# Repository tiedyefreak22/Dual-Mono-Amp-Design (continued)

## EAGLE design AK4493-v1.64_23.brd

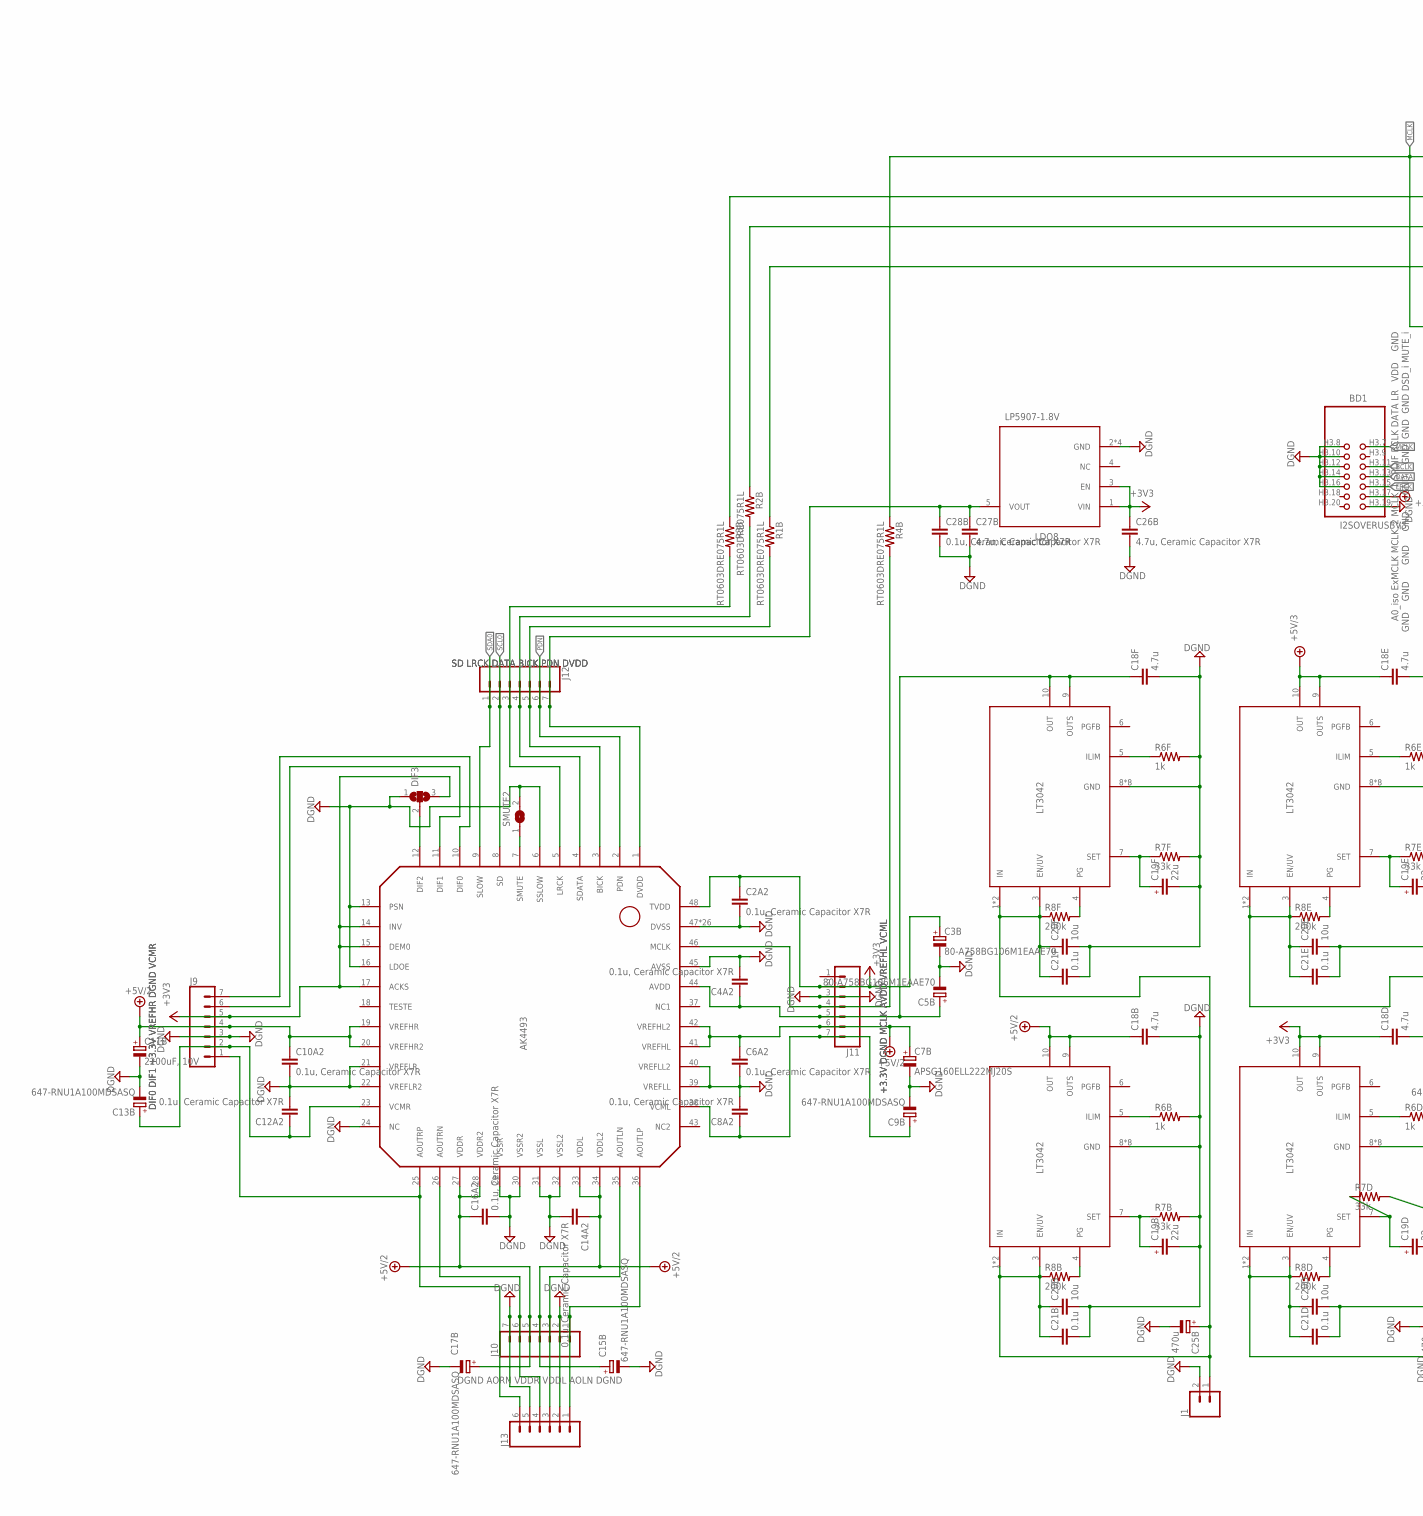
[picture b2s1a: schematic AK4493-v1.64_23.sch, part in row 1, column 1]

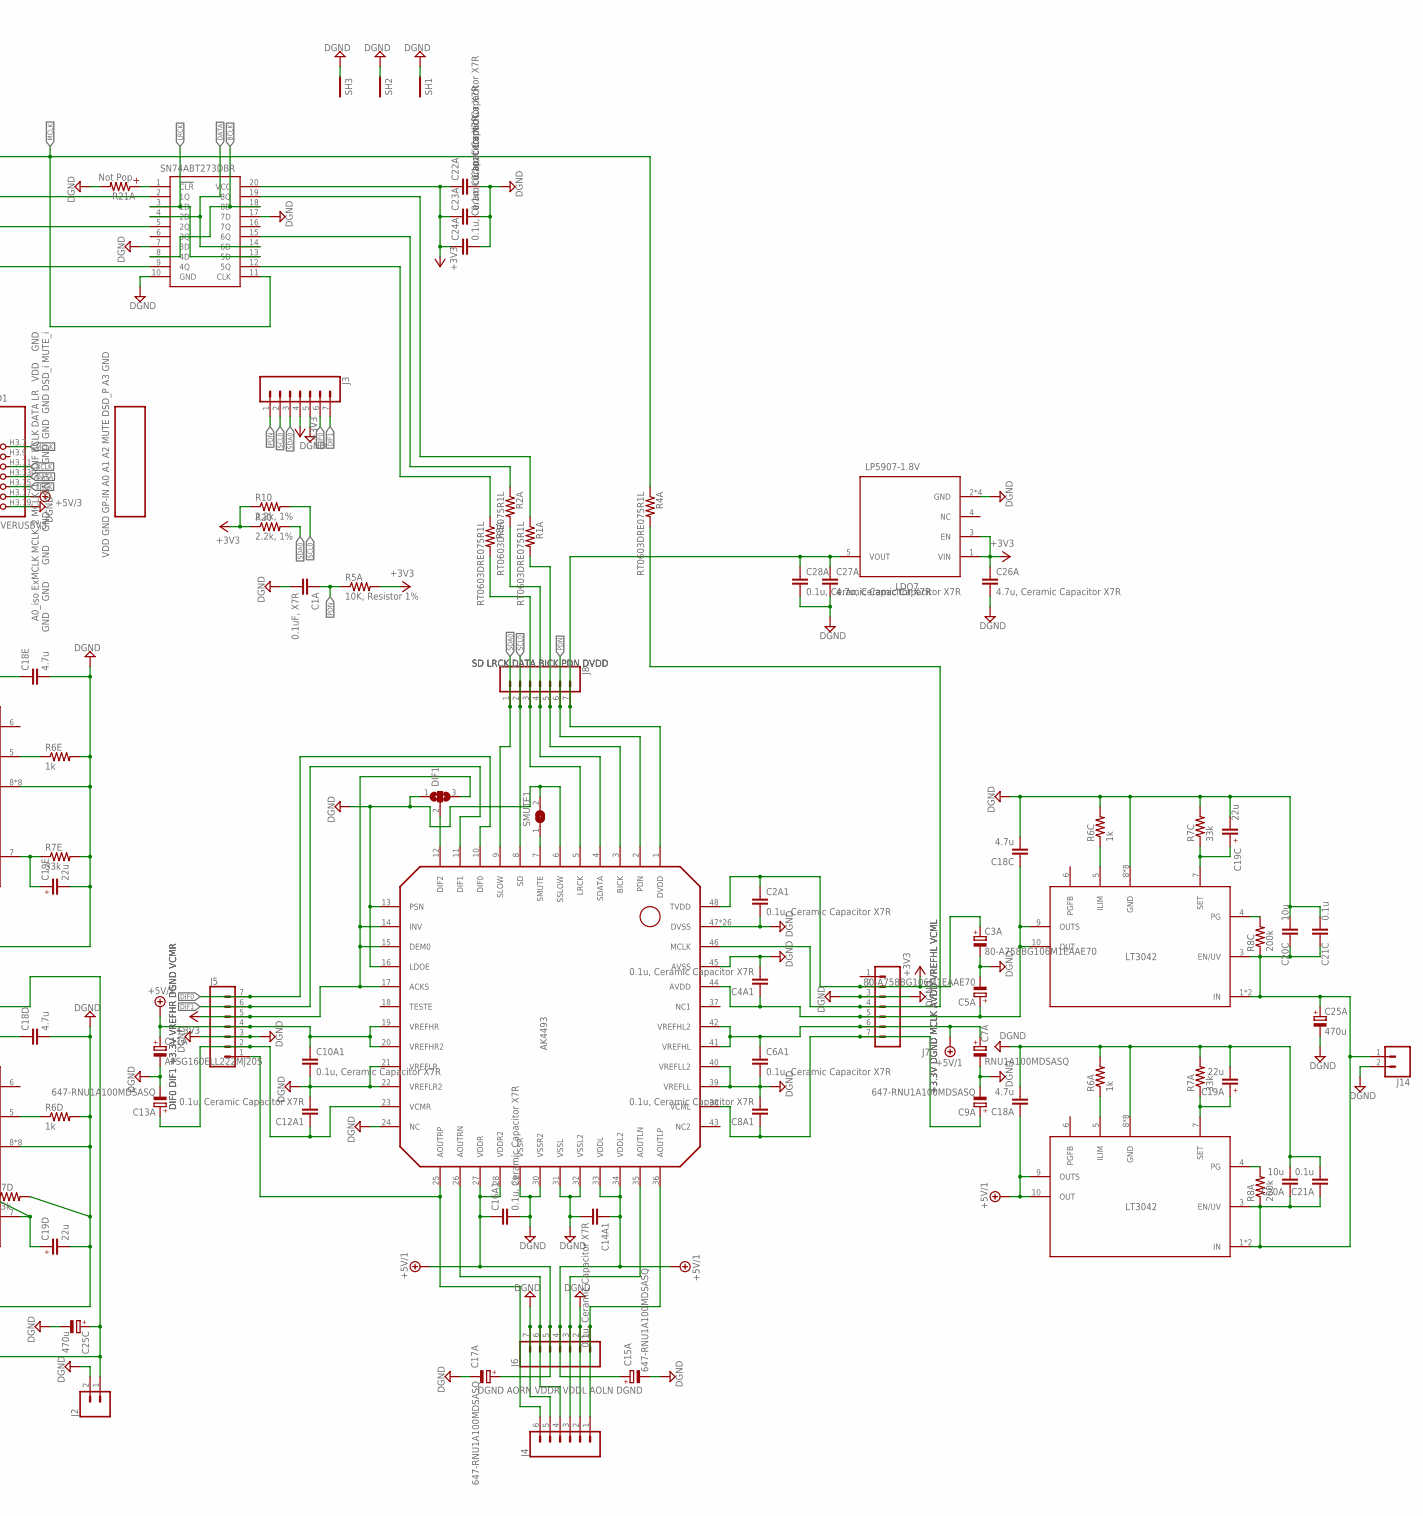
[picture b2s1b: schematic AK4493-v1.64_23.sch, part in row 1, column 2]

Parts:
BD1: I2SOVERUSBV3
C1A: 0.1uF, X7R; CAPC2012X135N
C2A1, C2A2, C4A1, C4A2, C6A1, C6A2, C8A1, C8A2, C10A1, C10A2, C12A1, C12A2, C14A1, C14A2, C16A1, C16A2: 0.1u, Ceramic Capacitor X7R; CAPC1608X95N
C3A: 80-A758BG106M1EAAE70; CAPPRD150W45D450H600
C3B, C5A, C5B: 80-A758BG106M1EAAE70; CAPPRD200W55D500H800
C7A: RNU1A100MDSASQ; CAPPRD150W45D450H600
C7B, C11A: APSG160ELL222MJ20S; CAPPRD500W60D1025H2150
C9A, C9B, C13A, C13B, C15A, C15B, C17A, C17B: 647-RNU1A100MDSASQ; CAPPRD150W45D450H600
C11B: 2200uF, 10V; CAPPRD500W60D1025H2150
C18A, C18B, C18C, C18D, C18E, C18F: 4.7u; CAPC2013X140N
C19A, C19B, C19C, C19D, C19E, C19F: 22u; C1206
C20A, C20B, C20C, C20D, C20E, C20F: 10u; CAPC2012X135N
C21A, C21B, C21C, C21D, C21E, C21F: 0.1u; CAPC2012X135N
C22A, C23A, C24A, C28A, C28B: 0.1u, Ceramic Capacitor X7R; CAPC2012X135N
C25A, C25B, C25C: 470u; CAPPRD350W60D825H1300
C26A, C26B, C27A, C27B: 4.7u, Ceramic Capacitor X7R; CAPC2013X140N
DIF1, DIF3: SJ2W; SJ_2
IC2, IC3: AK4493; LQFP48_
IC4A: SN74ABT273DBR; SOP65P780X200-20N
J1, J2, J14: CONN_02; 1X02
J3, J5, J6, J7, J8, J9, J10, J11, J12: CONN_07; 1X07
J4, J13: CONN_06SILK_FEMALE_PTH; 1X06
LDO1, LDO2, LDO3, LDO4, LDO5, LDO6: LT3042; SOP50P490X110-11N
LDO7, LDO8: LP5907-1.8V; SOT95P280X145-5N
R1A, R1B, R2A, R2B, R3A, R3B, R4A, R4B: RT0603DRE075R1L; RESC1608X55N
R5A: 10K, Resistor 1%; RESC2012X50N
R6A, R6B, R6C, R6D, R6E, R6F: 1k; RESC2012X60N
R7A, R7B, R7C, R7D, R7E, R7F: 33k; R0805
R8A, R8B, R8C, R8D, R8E, R8F: 200k; R0805
R10, R20: 2.2k, 1%; RCS0805_E3
R21A: Not Pop.; R0805-POL
SH1, SH2, SH3: SHORTA5; SHORT_ALL-50
SMUTE1, SMUTE2: SJ

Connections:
+3V3: C2A1.1, C2A2.1, C3A.1 (+), C3B.1 (+), C18D.1, C22A.1, C23A.1, C24A.1, C26A.1, C26B.1, DIF1.3, DIF3.3, IC2.14 (INV), IC2.15 (DEM0), IC2.17 (ACKS), IC2.48 (TVDD), IC3.14 (INV), IC3.15 (DEM0), IC3.17 (ACKS), IC3.48 (TVDD), IC4A.20 (VCC), J3.4, J5.5, J7.2, J9.5, J11.2, LDO4.9 (OUTS), LDO4.10 (OUT), LDO7.1 (VIN), LDO7.3 (EN), LDO8.1 (VIN), LDO8.3 (EN), R5A.2, R10.1, R20.1
+5V/1: C6A1.1, C7A.1 (+), C10A1.1, C11A.1 (+), C14A1.1, C15A.1 (+), C16A1.1, C17A.1 (+), C18A.1, IC2.19 (VREFHR), IC2.20 (VREFHR2), IC2.27 (VDDR), IC2.28 (VDDR2), IC2.33 (VDDL), IC2.34 (VDDL2), IC2.41 (VREFHL), IC2.42 (VREFHL2), J5.4, J6.4, J6.5, J7.6, LDO1.9 (OUTS), LDO1.10 (OUT)
+5V/2: C6A2.1, C7B.1 (+), C10A2.1, C11B.1 (+), C14A2.1, C15B.1 (+), C16A2.1, C17B.1 (+), C18B.1, IC3.19 (VREFHR), IC3.20 (VREFHR2), IC3.27 (VDDR), IC3.28 (VDDR2), IC3.33 (VDDL), IC3.34 (VDDL2), IC3.41 (VREFHL), IC3.42 (VREFHL2), J9.4, J10.4, J10.5, J11.6, LDO2.9 (OUTS), LDO2.10 (OUT)
+5V/3: BD1.H3.17, C18E.1, LDO5.9 (OUTS), LDO5.10 (OUT)
BCLK: BD1.H3.11, IC4A.8 (4D), IC4A.18 (8D)
DATA: BD1.H3.13, IC4A.4 (2D), IC4A.14 (6D)
DGND: BD1.H3.8, BD1.H3.10, BD1.H3.12, BD1.H3.14, BD1.H3.16, BD1.H3.19, C1A.2, C2A1.2, C2A2.2, C3A.2 (-), C3B.2 (-), C4A1.2, C4A2.2, C5A.2 (-), C5B.2 (-), C6A1.2, C6A2.2, C7A.2 (-), C7B.2 (-), C8A1.2, C8A2.2, C9A.2 (-), C9B.2 (-), C10A1.2, C10A2.2, C11A.2 (-), C11B.2 (-), C12A1.2, C12A2.2, C13A.2 (-), C13B.2 (-), C14A1.2, C14A2.2, C15A.2 (-), C15B.2 (-), C16A1.2, C16A2.2, C17A.2 (-), C17B.2 (-), C18A.2, C18B.2, C18C.2, C18D.2, C18E.2, C18F.2, C19A.2, C19A.DGND (2), C19B.2, C19B.DGND (2), C19C.2, C19C.DGND (2), C19D.2, C19D.DGND (2), C19E.2, C19E.DGND (2), C19F.2, C19F.DGND (2), C20A.2, C20B.2, C20C.2, C20D.2, C20E.2, C20F.2, C21A.2, C21B.2, C21C.2, C21D.2, C21E.2, C21F.2, C22A.2, C23A.2, C24A.2, C25A.2 (-), C25B.2 (-), C25C.2 (-), C26A.2, C26B.2, C27A.2, C27B.2, C28A.2, C28B.2, DIF1.1, DIF3.1, IC2.6 (SSLOW), IC2.13 (PSN), IC2.16 (LDOE), IC2.21 (VREFLR), IC2.22 (VREFLR2), IC2.24 (NC), IC2.29 (VSSR), IC2.30 (VSSR2), IC2.31 (VSSL), IC2.32 (VSSL2), IC2.39 (VREFLL), IC2.40 (VREFLL2), IC2.45 (AVSS), IC2.47 (DVSS), IC2.P$1 (DVSS), IC2.P$2 (DVSS), IC2.P$3 (DVSS), IC2.P$4 (DVSS), IC2.P$5 (DVSS), IC2.P$6 (DVSS), IC2.P$7 (DVSS), IC2.P$8 (DVSS), IC2.P$9 (DVSS), IC2.P$10 (DVSS), IC2.P$11 (DVSS), IC2.P$12 (DVSS), IC2.P$13 (DVSS), IC2.P$14 (DVSS), IC2.P$15 (DVSS), IC2.P$16 (DVSS), IC2.P$17 (DVSS), IC2.P$18 (DVSS), IC2.P$19 (DVSS), IC2.P$20 (DVSS), IC2.P$21 (DVSS), IC2.P$22 (DVSS), IC2.P$23 (DVSS), IC2.P$24 (DVSS), IC2.P$25 (DVSS), IC3.6 (SSLOW), IC3.13 (PSN), IC3.16 (LDOE), IC3.21 (VREFLR), IC3.22 (VREFLR2), IC3.24 (NC), IC3.29 (VSSR), IC3.30 (VSSR2), IC3.31 (VSSL), IC3.32 (VSSL2), IC3.39 (VREFLL), IC3.40 (VREFLL2), IC3.45 (AVSS), IC3.47 (DVSS), IC3.P$1 (DVSS), IC3.P$2 (DVSS), IC3.P$3 (DVSS), IC3.P$4 (DVSS), IC3.P$5 (DVSS), IC3.P$6 (DVSS), IC3.P$7 (DVSS), IC3.P$8 (DVSS), IC3.P$9 (DVSS), IC3.P$10 (DVSS), IC3.P$11 (DVSS), IC3.P$12 (DVSS), IC3.P$13 (DVSS), IC3.P$14 (DVSS), IC3.P$15 (DVSS), IC3.P$16 (DVSS), IC3.P$17 (DVSS), IC3.P$18 (DVSS), IC3.P$19 (DVSS), IC3.P$20 (DVSS), IC3.P$21 (DVSS), IC3.P$22 (DVSS), IC3.P$23 (DVSS), IC3.P$24 (DVSS), IC3.P$25 (DVSS), IC4A.7 (3D), IC4A.10 (GND), IC4A.17 (7D), J1.2, J2.2, J3.5, J4.2, J4.5, J5.3, J6.2, J6.7, J7.3, J9.3, J10.2, J10.7, J11.3, J13.2, J13.5, J14.2, LDO1.8 (GND), LDO1.11 (GND), LDO1.P$1 (GND), LDO1.P$2 (GND), LDO1.P$3 (GND), LDO1.P$4 (GND), LDO1.P$5 (GND), LDO1.P$6 (GND), LDO2.8 (GND), LDO2.11 (GND), LDO2.P$1 (GND), LDO2.P$2 (GND), LDO2.P$3 (GND), LDO2.P$4 (GND), LDO2.P$5 (GND), LDO2.P$6 (GND), LDO3.8 (GND), LDO3.11 (GND), LDO3.P$1 (GND), LDO3.P$2 (GND), LDO3.P$3 (GND), LDO3.P$4 (GND), LDO3.P$5 (GND), LDO3.P$6 (GND), LDO4.8 (GND), LDO4.11 (GND), LDO4.P$1 (GND), LDO4.P$2 (GND), LDO4.P$3 (GND), LDO4.P$4 (GND), LDO4.P$5 (GND), LDO4.P$6 (GND), LDO5.8 (GND), LDO5.11 (GND), LDO5.P$1 (GND), LDO5.P$2 (GND), LDO5.P$3 (GND), LDO5.P$4 (GND), LDO5.P$5 (GND), LDO5.P$6 (GND), LDO6.8 (GND), LDO6.11 (GND), LDO6.P$1 (GND), LDO6.P$2 (GND), LDO6.P$3 (GND), LDO6.P$4 (GND), LDO6.P$5 (GND), LDO6.P$6 (GND), LDO7.2 (GND), LDO7.DGND (GND), LDO7.DGND2 (GND), LDO7.DGND3 (GND), LDO8.2 (GND), LDO8.DGND (GND), LDO8.DGND2 (GND), LDO8.DGND3 (GND), R6A.2, R6B.2, R6C.2, R6D.2, R6E.2, R6F.2, R7A.2, R7B.2, R7C.2, R7D.2, R7E.2, R7F.2, R21A.2, R21A.DGND (2), SH1.1, SH2.1, SH3.1, SMUTE1.2, SMUTE2.2
DIF0: IC2.10 (DIF0), J3.6, J5.7
DIF1: IC2.11 (DIF1), J3.7, J5.6
LRCK: BD1.H3.15, IC4A.3 (1D), IC4A.13 (5D)
MCLK: BD1.H3.7, IC4A.11 (CLK), R4A.1, R4B.1
unnamed: IC4A.1 (!CLR), R21A.1
unnamed: C8A2.1, C9B.1 (+), IC3.38 (VCML), J11.7
unnamed: C4A1.1, C5A.1 (+), C18C.1, IC2.44 (AVDD), J7.5, LDO3.9 (OUTS), LDO3.10 (OUT)
unnamed: LDO3.5 (ILIM), R6C.1
unnamed: LDO4.5 (ILIM), R6D.1
unnamed: C19D.1, LDO4.7 (SET), R7D.1
unnamed: LDO4.4 (PG), R8D.2
unnamed: LDO5.5 (ILIM), R6E.1
unnamed: C19E.1, LDO5.7 (SET), R7E.1
unnamed: IC3.46 (MCLK), J11.4, R4B.2
unnamed: LDO5.4 (PG), R8E.2
unnamed: C20D.1, C20E.1, C21D.1, C21E.1, C25C.1 (+), J2.1, LDO4.1 (IN), LDO4.2 (IN), LDO4.3 (EN/UV), LDO5.1 (IN), LDO5.2 (IN), LDO5.3 (EN/UV), R8D.1, R8E.1
unnamed: LDO1.5 (ILIM), R6A.1
unnamed: IC2.5 (LRCK), J8.3, R3A.2
unnamed: IC2.4 (SDATA), J8.4, R2A.2
unnamed: IC2.3 (BICK), J8.5, R1A.2
unnamed: C19A.1, LDO1.7 (SET), R7A.1
unnamed: IC4A.19 (8Q), R1A.1
unnamed: IC4A.15 (6Q), R2A.1
unnamed: IC4A.12 (5Q), R3A.1
unnamed: IC2.26 (AOUTRN), J4.4, J6.6
unnamed: IC3.3 (BICK), J12.5, R1B.2
unnamed: IC3.4 (SDATA), J12.4, R2B.2
unnamed: IC3.5 (LRCK), J12.3, R3B.2
unnamed: IC4A.9 (4Q), R1B.1
unnamed: IC4A.5 (2Q), R2B.1
unnamed: IC4A.2 (1Q), R3B.1
unnamed: LDO1.4 (PG), R8A.2
unnamed: LDO6.5 (ILIM), R6F.1
unnamed: C19F.1, LDO6.7 (SET), R7F.1
unnamed: C27A.1, C28A.1, IC2.1 (DVDD), J8.7, LDO7.5 (VOUT)
unnamed: LDO6.4 (PG), R8F.2
unnamed: C20A.1, C20C.1, C21A.1, C21C.1, C25A.1 (+), J14.1, LDO1.1 (IN), LDO1.2 (IN), LDO1.3 (EN/UV), LDO3.1 (IN), LDO3.2 (IN), LDO3.3 (EN/UV), R8A.1, R8C.1
unnamed: C4A2.1, C5B.1 (+), C18F.1, IC3.44 (AVDD), J11.5, LDO6.9 (OUTS), LDO6.10 (OUT)
unnamed: C19C.1, LDO3.7 (SET), R7C.1
unnamed: LDO3.4 (PG), R8C.2
unnamed: LDO2.5 (ILIM), R6B.1
unnamed: C19B.1, LDO2.7 (SET), R7B.1
unnamed: LDO2.4 (PG), R8B.2
unnamed: C20B.1, C20F.1, C21B.1, C21F.1, C25B.1 (+), J1.1, LDO2.1 (IN), LDO2.2 (IN), LDO2.3 (EN/UV), LDO6.1 (IN), LDO6.2 (IN), LDO6.3 (EN/UV), R8B.1, R8F.1
unnamed: C27B.1, C28B.1, IC3.1 (DVDD), J12.7, LDO8.5 (VOUT)
unnamed: C12A1.1, C13A.1 (+), IC2.23 (VCMR), J5.2
unnamed: IC3.36 (AOUTLP), J10.1, J13.1
unnamed: IC3.25 (AOUTRP), J9.1, J13.6
unnamed: IC3.10 (DIF0), J9.7
unnamed: IC2.36 (AOUTLP), J4.1, J6.1
unnamed: IC2.35 (AOUTLN), J4.3, J6.3
unnamed: IC3.35 (AOUTLN), J10.3, J13.3
unnamed: IC3.26 (AOUTRN), J10.6, J13.4
unnamed: IC2.25 (AOUTRP), J4.6, J5.1
unnamed: IC2.46 (MCLK), J7.4, R4A.2
unnamed: C12A2.1, C13B.1 (+), IC3.23 (VCMR), J9.2
unnamed: C8A1.1, C9A.1 (+), IC2.38 (VCML), J7.7
unnamed: DIF1.2, IC2.12 (DIF2)
unnamed: IC2.7 (SMUTE), SMUTE1.1
unnamed: DIF3.2, IC3.12 (DIF2)
unnamed: IC3.7 (SMUTE), SMUTE2.1
unnamed: IC3.11 (DIF1), J9.6
PDN: C1A.1, IC2.2 (PDN), IC3.2 (PDN), J3.1, J8.6, J12.6, R5A.1
SCL0: IC2.8 (SD), IC3.8 (SD), J3.2, J8.2, J12.2, R10.2
SDA0: IC2.9 (SLOW), IC3.9 (SLOW), J3.3, J8.1, J12.1, R20.2

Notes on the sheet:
+3.3V DGND MCLK AVDD VREFHL VCML
DIF0 DIF1 +3.3V VREFHR DGND VCMR
SD LRCK DATA BICK PDN DVDD
DGND AORN VDDR VDDL AOLN DGND

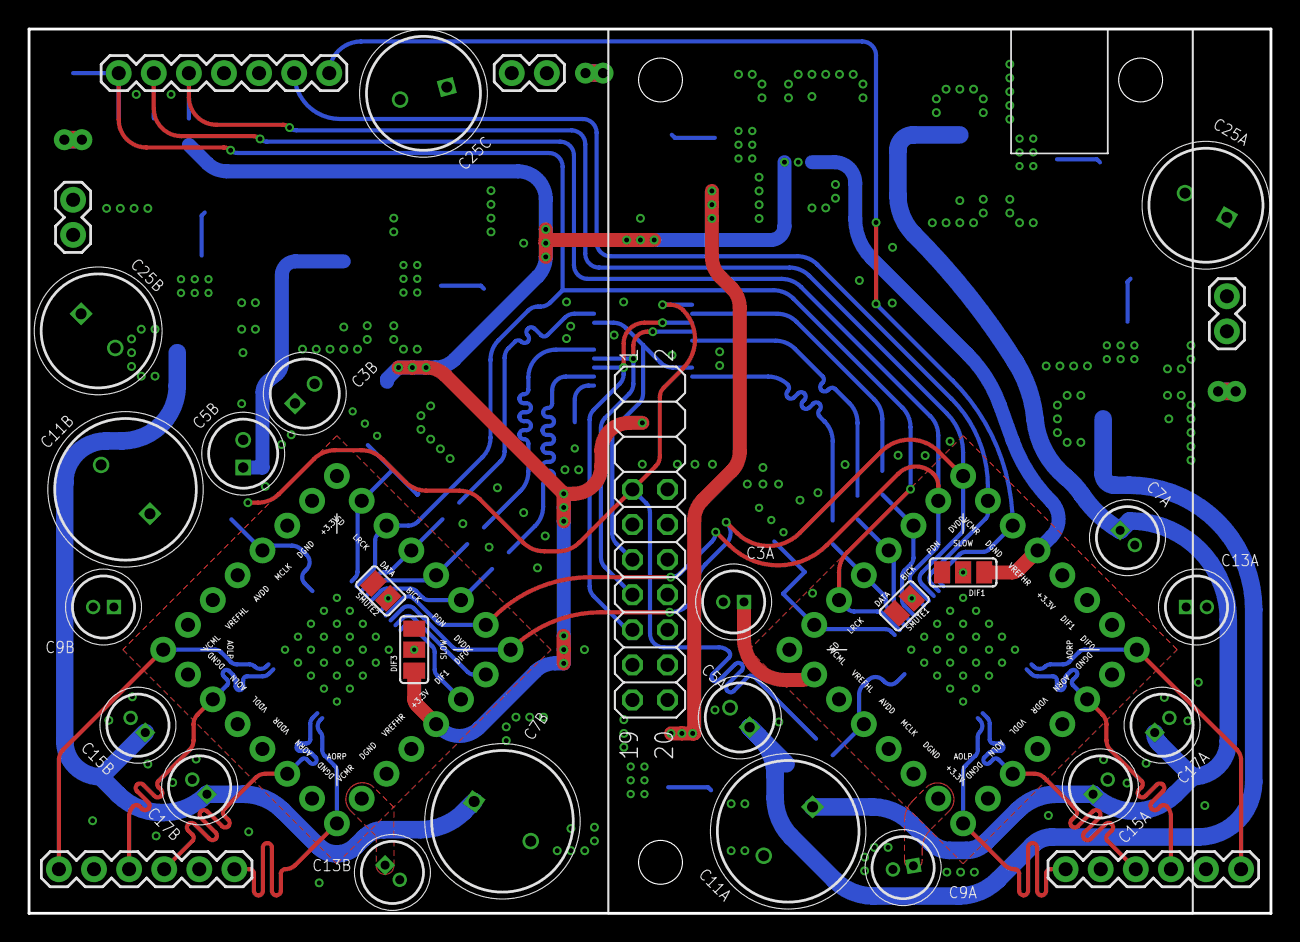
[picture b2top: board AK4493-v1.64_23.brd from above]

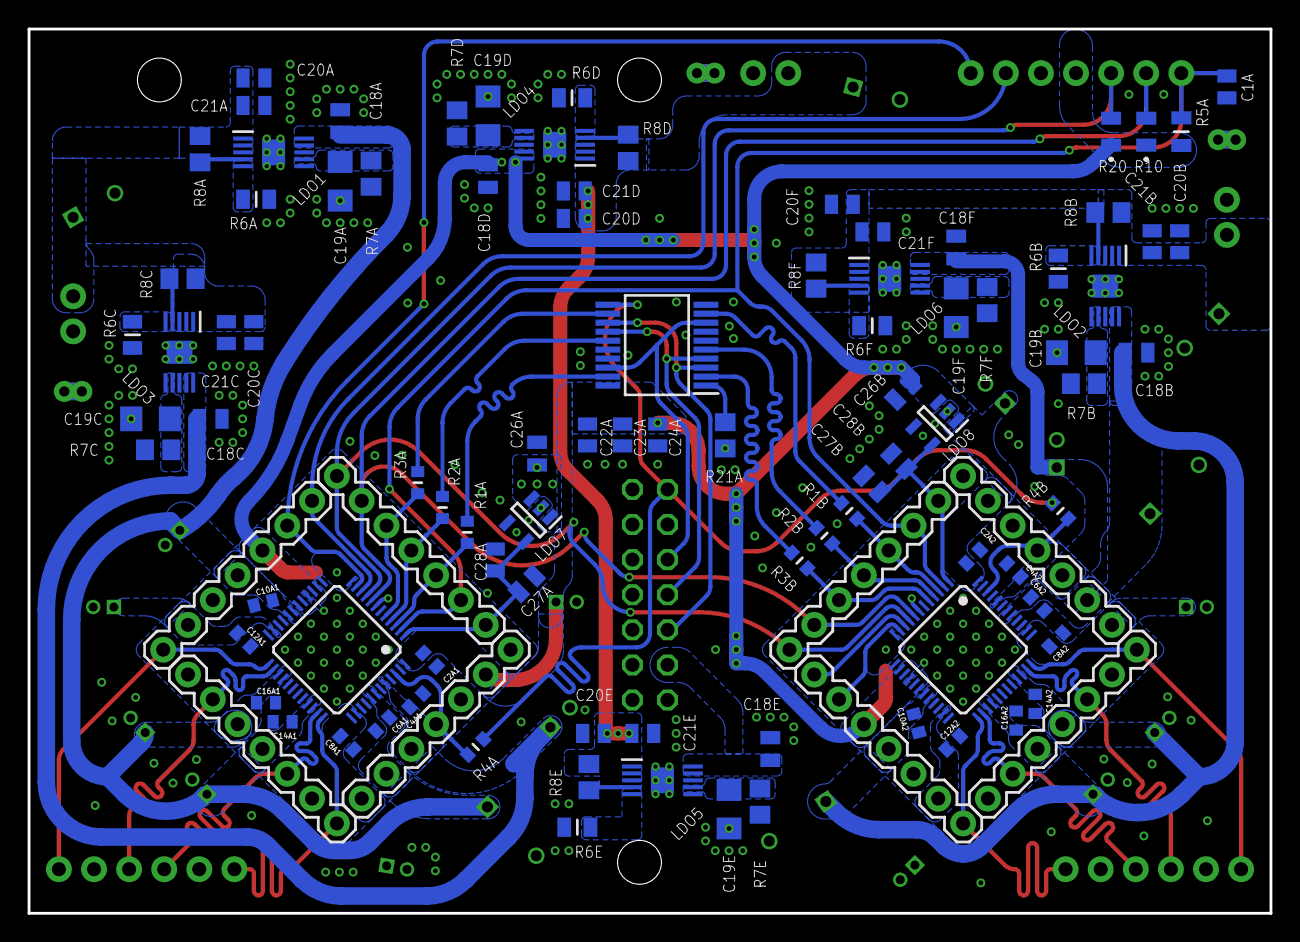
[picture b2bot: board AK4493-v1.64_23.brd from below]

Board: 2 copper layers, 89.9 x 64.0 mm, 132 parts (99 on the bottom side), 72 nets.
